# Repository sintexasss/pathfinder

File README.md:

# pathfinder
pathfinder proyect

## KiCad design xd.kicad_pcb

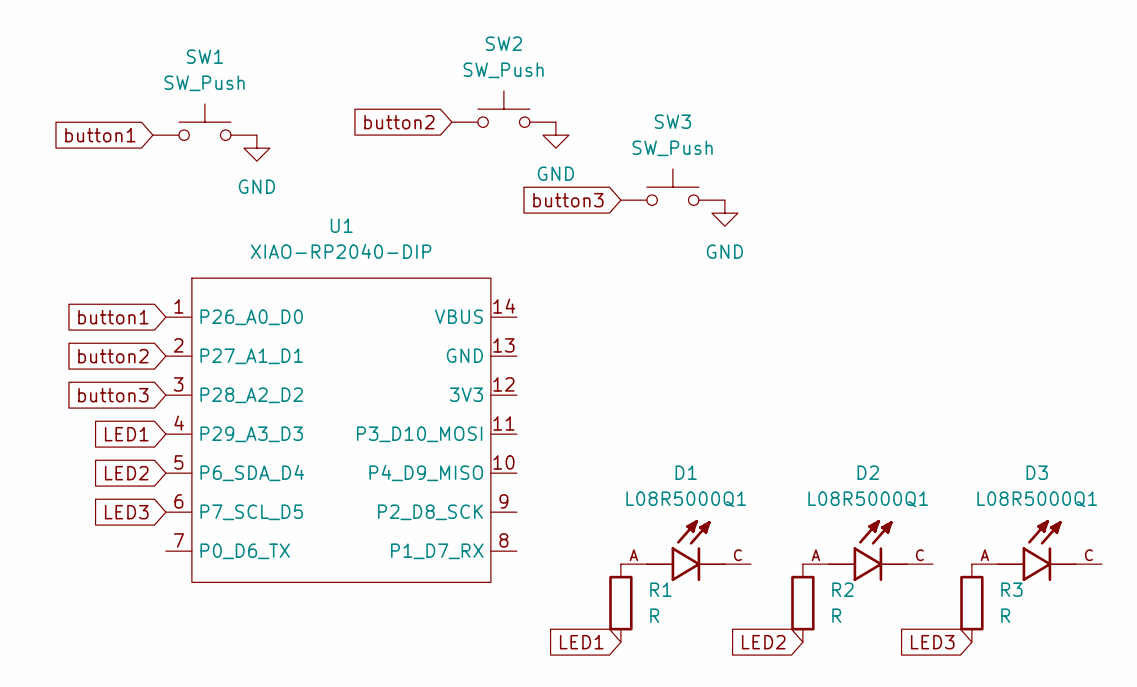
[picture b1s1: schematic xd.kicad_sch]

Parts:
D1, D2, D3: L08R5000Q1; LEDRD254W57D500H1070; PARTREV NA
R1, R2, R3: R; R_Axial_DIN0207_L6.3mm_D2.5mm_P7.62mm_Horizontal
SW1, SW2, SW3: SW_Push; SW_PUSH_6mm
U1: XIAO-RP2040-DIP

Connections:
GND: SW1.2, SW2.2, SW3.2
LED1: R1.2, U1.4 (P29_A3_D3)
LED2: R2.2, U1.5 (P6_SDA_D4)
LED3: R3.2, U1.6 (P7_SCL_D5)
unnamed: D1.A, R1.1
unnamed: D2.A, R2.1
unnamed: D3.A, R3.1
button1: SW1.1, U1.1 (P26_A0_D0)
button2: SW2.1, U1.2 (P27_A1_D1)
button3: SW3.1, U1.3 (P28_A2_D2)

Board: 2 copper layers, 10 parts (0 on the bottom side), 10 nets, no tracks yet.
